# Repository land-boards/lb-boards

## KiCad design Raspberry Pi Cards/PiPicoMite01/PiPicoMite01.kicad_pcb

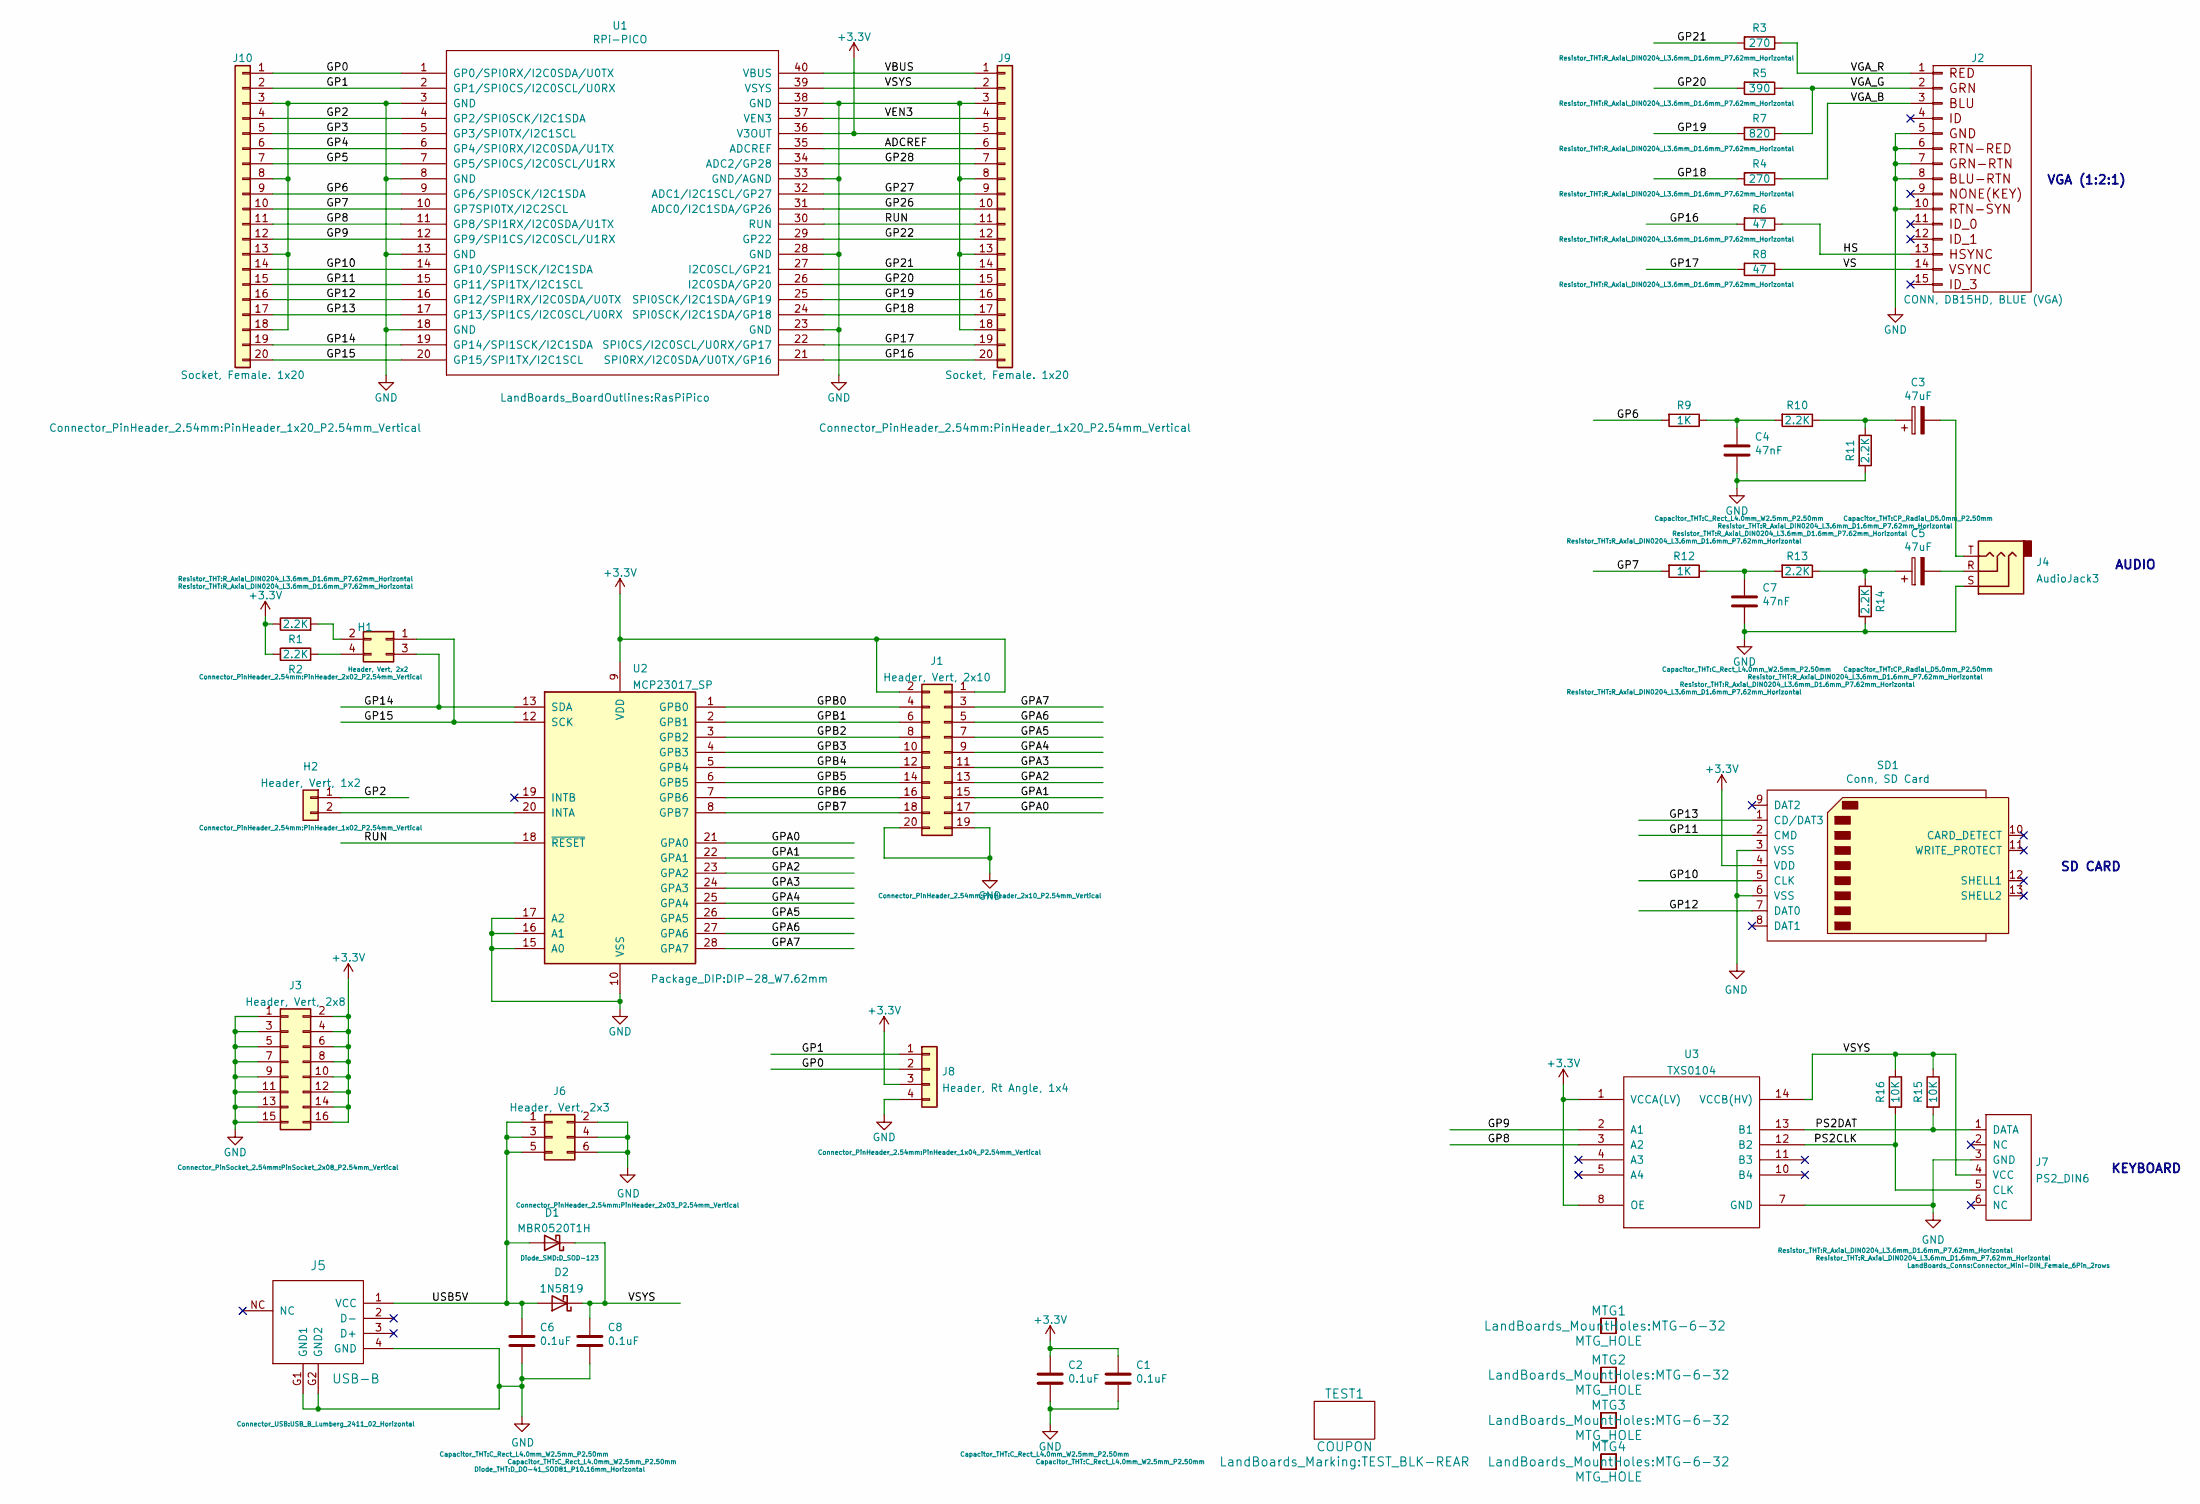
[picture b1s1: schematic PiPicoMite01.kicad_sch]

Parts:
C1, C2, C6, C8: 0.1uF; C_Rect_L4.0mm_W2.5mm_P2.50mm
C3, C5: 47uF; CP_Radial_D5.0mm_P2.50mm
C4, C7: 47nF; C_Rect_L4.0mm_W2.5mm_P2.50mm
D1: MBR0520T1H; D_SOD-123
D2: 1N5819; D_DO-41_SOD81_P10.16mm_Horizontal
H1: Header, Vert, 2x2; PinHeader_2x02_P2.54mm_Vertical
H2: Header, Vert, 1x2; PinHeader_1x02_P2.54mm_Vertical
J1: Header, Vert, 2x10; PinHeader_2x10_P2.54mm_Vertical
J2: CONN, DB15HD, BLUE (VGA); DB_15F-VGA-fixed
J3: Header, Vert, 2x8; PinSocket_2x08_P2.54mm_Vertical
J4: AudioJack3; Jack_3.5mm_CUI_SJ1-3523N_Horizontal
J5: USB-B; USB_B_Lumberg_2411_02_Horizontal
J6: Header, Vert, 2x3; PinHeader_2x03_P2.54mm_Vertical
J7: PS2_DIN6; Connector_Mini-DIN_Female_6Pin_2rows
J8: Header, Rt Angle, 1x4; PinHeader_1x04_P2.54mm_Vertical
J9, J10: Socket, Female. 1x20; PinHeader_1x20_P2.54mm_Vertical
MTG1, MTG2, MTG3, MTG4: MTG_HOLE; MTG-6-32
R1, R2, R10, R11, R13, R14: 2.2K; R_Axial_DIN0204_L3.6mm_D1.6mm_P7.62mm_Horizontal
R3, R4: 270; R_Axial_DIN0204_L3.6mm_D1.6mm_P7.62mm_Horizontal
R5: 390; R_Axial_DIN0204_L3.6mm_D1.6mm_P7.62mm_Horizontal
R6, R8: 47; R_Axial_DIN0204_L3.6mm_D1.6mm_P7.62mm_Horizontal
R7: 820; R_Axial_DIN0204_L3.6mm_D1.6mm_P7.62mm_Horizontal
R9, R12: 1K; R_Axial_DIN0204_L3.6mm_D1.6mm_P7.62mm_Horizontal
R15, R16: 10K; R_Axial_DIN0204_L3.6mm_D1.6mm_P7.62mm_Horizontal
SD1: Conn, SD Card; SD_CARD
TEST1: COUPON; TEST_BLK-REAR
U1: RPi-PICO; RasPiPico
U2: MCP23017_SP; DIP-28_W7.62mm
U3: TXS0104; SOIC-14_3.9x8.7mm_P1.27mm

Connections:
+3V3: C1.1, C2.1, J1.1, J1.2, J3.2, J3.4, J3.6, J3.8, J3.10, J3.12, J3.14, J3.16, J8.3, J9.5, R1.1, R2.1, SD1.4 (VDD), U1.36 (V3OUT), U2.9 (VDD), U3.1 (VCCA(LV)), U3.8 (OE)
/ADCREF: J9.6, U1.35 (ADCREF)
/GP0: J8.2, J10.1, U1.1 (GP0/SPI0RX/I2C0SDA/U0TX)
/GP1: J8.1, J10.2, U1.2 (GP1/SPI0CS/I2C0SCL/U0RX)
/GP2: H2.1, J10.4, U1.4 (GP2/SPI0SCK/I2C1SDA)
/GP3: J10.5, U1.5 (GP3/SPI0TX/I2C1SCL)
/GP4: J10.6, U1.6 (GP4/SPI0RX/I2C0SDA/U1TX)
/GP5: J10.7, U1.7 (GP5/SPI0CS/I2C0SCL/U1RX)
/GP6: J10.9, R9.2, U1.9 (GP6/SPI0SCK/I2C1SDA)
/GP7: J10.10, R12.2, U1.10 (GP7SPI0TX/I2C2SCL)
/GP8: J10.11, U1.11 (GP8/SPI1RX/I2C0SDA/U1TX), U3.3 (A2)
/GP9: J10.12, U1.12 (GP9/SPI1CS/I2C0SCL/U1RX), U3.2 (A1)
/GP10: J10.14, SD1.5 (CLK), U1.14 (GP10/SPI1SCK/I2C1SDA)
/GP11: J10.15, SD1.2 (CMD), U1.15 (GP11/SPI1TX/I2C1SCL)
/GP12: J10.16, SD1.7 (DAT0), U1.16 (GP12/SPI1RX/I2C0SDA/U0TX)
/GP13: J10.17, SD1.1 (CD/DAT3), U1.17 (GP13/SPI1CS/I2C0SCL/U0RX)
/GP14: H1.3, J10.19, U1.19 (GP14/SPI1SCK/I2C1SDA), U2.13 (SDA)
/GP15: H1.1, J10.20, U1.20 (GP15/SPI1TX/I2C1SCL), U2.12 (SCK)
/GP16: J9.20, R6.2, U1.21 (SPI0RX/I2C0SDA/U0TX/GP16)
/GP17: J9.19, R8.2, U1.22 (SPI0CS/I2C0SCL/U0RX/GP17)
/GP18: J9.17, R4.2, U1.24 (SPI0SCK/I2C1SDA/GP18)
/GP19: J9.16, R7.2, U1.25 (SPI0SCK/I2C1SDA/GP19)
/GP20: J9.15, R5.2, U1.26 (I2C0SDA/GP20)
/GP21: J9.14, R3.2, U1.27 (I2C0SCL/GP21)
/GP22: J9.12, U1.29 (GP22)
/GP26: J9.10, U1.31 (ADC0/I2C1SDA/GP26)
/GP27: J9.9, U1.32 (ADC1/I2C1SCL/GP27)
/GP28: J9.7, U1.34 (ADC2/GP28)
/GPA0: J1.17, U2.21 (GPA0)
/GPA1: J1.15, U2.22 (GPA1)
/GPA2: J1.13, U2.23 (GPA2)
/GPA3: J1.11, U2.24 (GPA3)
/GPA4: J1.9, U2.25 (GPA4)
/GPA5: J1.7, U2.26 (GPA5)
/GPA6: J1.5, U2.27 (GPA6)
/GPA7: J1.3, U2.28 (GPA7)
/GPB0: J1.4, U2.1 (GPB0)
/GPB1: J1.6, U2.2 (GPB1)
/GPB2: J1.8, U2.3 (GPB2)
/GPB3: J1.10, U2.4 (GPB3)
/GPB4: J1.12, U2.5 (GPB4)
/GPB5: J1.14, U2.6 (GPB5)
/GPB6: J1.16, U2.7 (GPB6)
/GPB7: J1.18, U2.8 (GPB7)
/HS: J2.13, R6.1
/PS2CLK: J7.5 (CLK), R16.2, U3.12 (B2)
/PS2DAT: J7.1 (DATA), R15.2, U3.13 (B1)
/RUN: J9.11, U1.30 (RUN), U2.18 (~RESET)
/USB5V: C6.1, D1.2 (A), D2.2 (A), J5.1 (VCC), J6.1, J6.3, J6.5
/VBUS: J9.1, U1.40 (VBUS)
/VEN3: J9.4, U1.37 (VEN3)
/VGA_B: J2.3, R4.1
/VGA_G: J2.2, R5.1, R7.1
/VGA_R: J2.1, R3.1
/VS: J2.14, R8.1
/VSYS: C8.1, D1.1 (K), D2.1 (K), J7.4 (VCC), J9.2, R15.1, R16.1, U1.39 (VSYS), U3.14 (VCCB(HV))
GND: C1.2, C2.2, C4.2, C6.2, C7.2, C8.2, J1.19, J1.20, J2.5, J2.6, J2.7, J2.8, J2.10, J3.1, J3.3, J3.5, J3.7, J3.9, J3.11, J3.13, J3.15, J4.S, J5.4 (GND), J5.G1 (GND1), J5.G2 (GND2), J6.2, J6.4, J6.6, J7.3 (GND), J8.4, J9.3, J9.8, J9.13, J9.18, J10.3, J10.8, J10.13, J10.18, R11.2, R14.1, SD1.3 (VSS), SD1.6 (VSS), U1.3 (GND), U1.8 (GND), U1.13 (GND), U1.18 (GND), U1.23 (GND), U1.28 (GND), U1.33 (GND/AGND), U1.38 (GND), U2.10 (VSS), U2.15 (A0), U2.16 (A1), U2.17 (A2), U3.7 (GND)
unnamed: C3.1, R10.1, R11.1
unnamed: C3.2, J4.T
unnamed: C4.1, R9.1, R10.2
unnamed: C5.1, R13.1, R14.2
unnamed: C5.2, J4.R
unnamed: C7.1, R12.1, R13.2
unnamed: H1.2, R1.2
unnamed: H1.4, R2.2
unnamed: H2.2, U2.20 (INTA)

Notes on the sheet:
KEYBOARD
AUDIO
VGA (1:2:1)
SD CARD

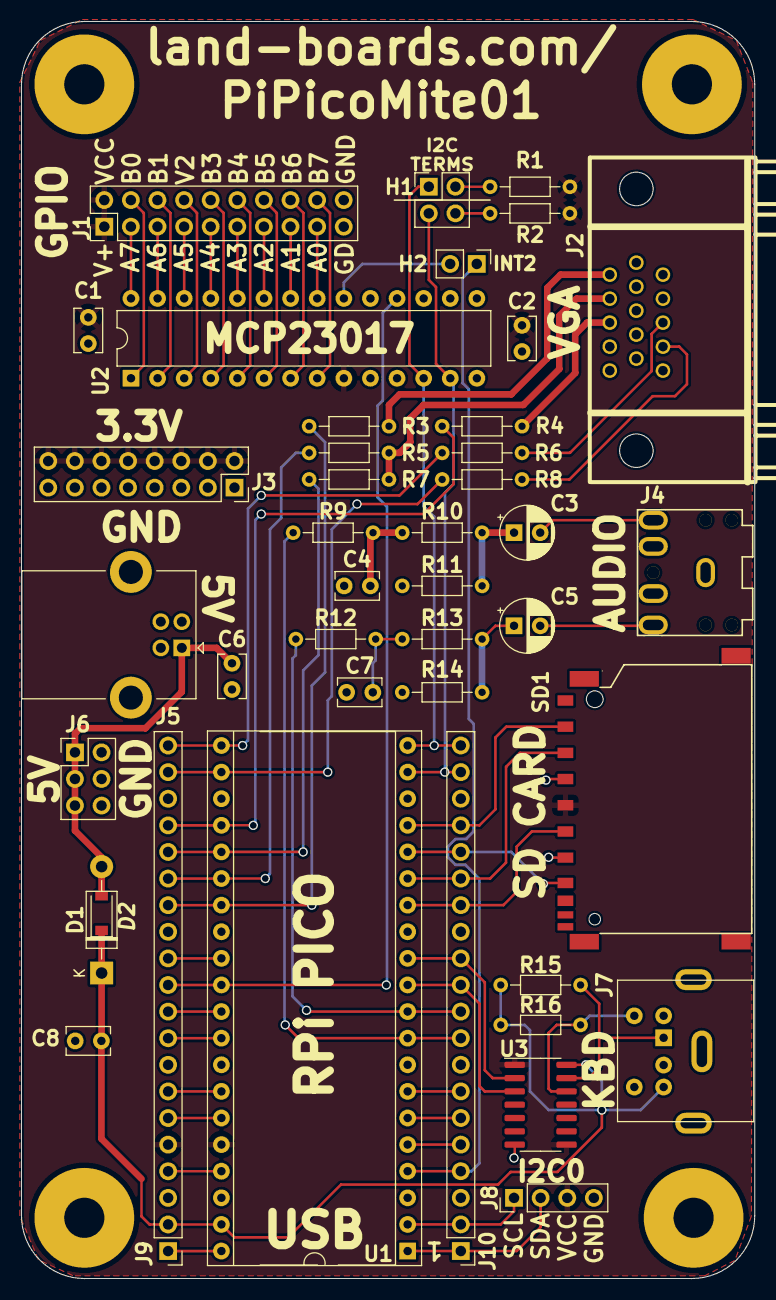
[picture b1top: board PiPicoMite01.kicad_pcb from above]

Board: 2 copper layers, 70.0 x 120.0 mm, 47 parts (0 on the bottom side), 66 nets.

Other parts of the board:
TEST: COUPON; TEST_BLK-REAR

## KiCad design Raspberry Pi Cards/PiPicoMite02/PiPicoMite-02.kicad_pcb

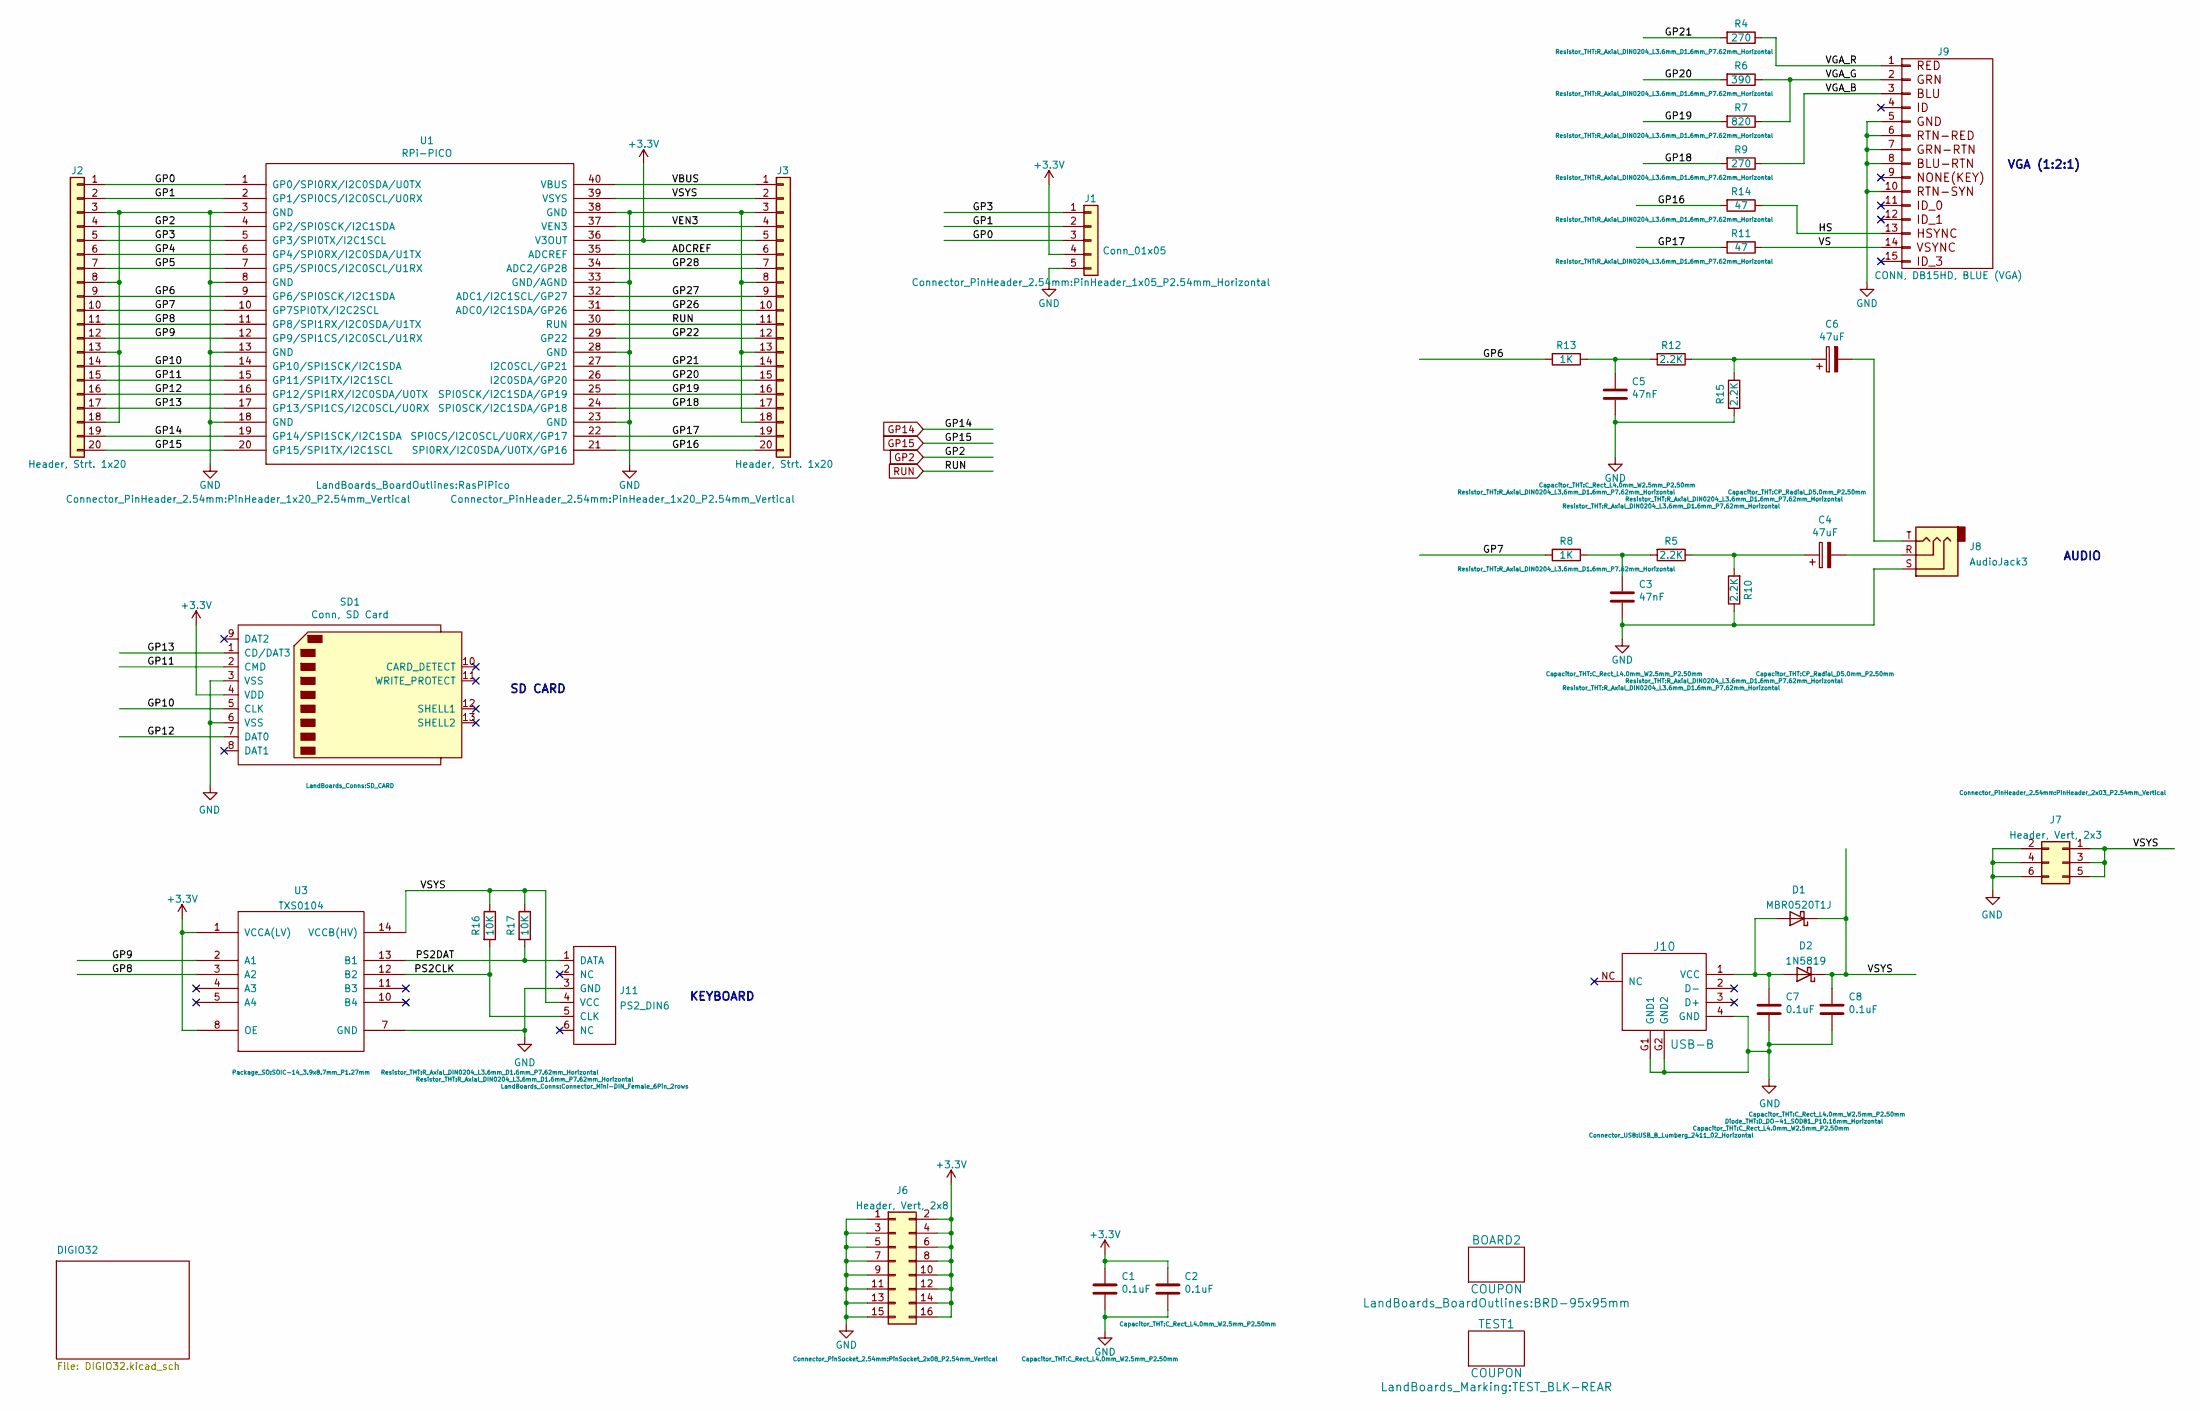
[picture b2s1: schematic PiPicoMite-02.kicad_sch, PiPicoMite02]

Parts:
BOARD2: COUPON; BRD-95x95mm
C1, C2, C7, C8: 0.1uF; C_Rect_L4.0mm_W2.5mm_P2.50mm
C3, C5: 47nF; C_Rect_L4.0mm_W2.5mm_P2.50mm
C4, C6: 47uF; CP_Radial_D5.0mm_P2.50mm
D1: MBR0520T1J; D_SOD-123
D2: 1N5819; D_DO-41_SOD81_P10.16mm_Horizontal
J1: Conn_01x05; PinHeader_1x05_P2.54mm_Horizontal
J2, J3: Header, Strt. 1x20; PinHeader_1x20_P2.54mm_Vertical
J6: Header, Vert, 2x8; PinSocket_2x08_P2.54mm_Vertical
J7: Header, Vert, 2x3; PinHeader_2x03_P2.54mm_Vertical
J8: AudioJack3; Jack_3.5mm_CUI_SJ1-3523N_Horizontal
J9: CONN, DB15HD, BLUE (VGA); DB_15F-VGA-fixed
J10: USB-B; USB_B_Lumberg_2411_02_Horizontal
J11: PS2_DIN6; Connector_Mini-DIN_Female_6Pin_2rows
R4, R9: 270; R_Axial_DIN0204_L3.6mm_D1.6mm_P7.62mm_Horizontal
R5, R10, R12, R15: 2.2K; R_Axial_DIN0204_L3.6mm_D1.6mm_P7.62mm_Horizontal
R6: 390; R_Axial_DIN0204_L3.6mm_D1.6mm_P7.62mm_Horizontal
R7: 820; R_Axial_DIN0204_L3.6mm_D1.6mm_P7.62mm_Horizontal
R8, R13: 1K; R_Axial_DIN0204_L3.6mm_D1.6mm_P7.62mm_Horizontal
R11, R14: 47; R_Axial_DIN0204_L3.6mm_D1.6mm_P7.62mm_Horizontal
R16, R17: 10K; R_Axial_DIN0204_L3.6mm_D1.6mm_P7.62mm_Horizontal
SD1: Conn, SD Card; SD_CARD
TEST1: COUPON; TEST_BLK-REAR
U1: RPi-PICO; RasPiPico
U3: TXS0104; SOIC-14_3.9x8.7mm_P1.27mm

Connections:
+3V3: C1.1, C2.1, J1.4, J3.5, J6.2, J6.4, J6.6, J6.8, J6.10, J6.12, J6.14, J6.16, SD1.4 (VDD), U1.36 (V3OUT), U3.1 (VCCA(LV)), U3.8 (OE); also elsewhere on the board
/ADCREF: J3.6, U1.35 (ADCREF)
/GP0: J1.3, J2.1, U1.1 (GP0/SPI0RX/I2C0SDA/U0TX)
/GP1: J1.2, J2.2, U1.2 (GP1/SPI0CS/I2C0SCL/U0RX)
/GP3: J1.1, J2.5, U1.5 (GP3/SPI0TX/I2C1SCL)
/GP4: J2.6, U1.6 (GP4/SPI0RX/I2C0SDA/U1TX)
/GP5: J2.7, U1.7 (GP5/SPI0CS/I2C0SCL/U1RX)
/GP6: J2.9, R13.2, U1.9 (GP6/SPI0SCK/I2C1SDA)
/GP7: J2.10, R8.2, U1.10 (GP7SPI0TX/I2C2SCL)
/GP8: J2.11, U1.11 (GP8/SPI1RX/I2C0SDA/U1TX), U3.3 (A2)
/GP9: J2.12, U1.12 (GP9/SPI1CS/I2C0SCL/U1RX), U3.2 (A1)
/GP10: J2.14, SD1.5 (CLK), U1.14 (GP10/SPI1SCK/I2C1SDA)
/GP11: J2.15, SD1.2 (CMD), U1.15 (GP11/SPI1TX/I2C1SCL)
/GP12: J2.16, SD1.7 (DAT0), U1.16 (GP12/SPI1RX/I2C0SDA/U0TX)
/GP13: J2.17, SD1.1 (CD/DAT3), U1.17 (GP13/SPI1CS/I2C0SCL/U0RX)
/GP16: J3.20, R14.2, U1.21 (SPI0RX/I2C0SDA/U0TX/GP16)
/GP17: J3.19, R11.2, U1.22 (SPI0CS/I2C0SCL/U0RX/GP17)
/GP18: J3.17, R9.2, U1.24 (SPI0SCK/I2C1SDA/GP18)
/GP19: J3.16, R7.2, U1.25 (SPI0SCK/I2C1SDA/GP19)
/GP20: J3.15, R6.2, U1.26 (I2C0SDA/GP20)
/GP21: J3.14, R4.2, U1.27 (I2C0SCL/GP21)
/GP22: J3.12, U1.29 (GP22)
/GP26: J3.10, U1.31 (ADC0/I2C1SDA/GP26)
/GP27: J3.9, U1.32 (ADC1/I2C1SCL/GP27)
/GP28: J3.7, U1.34 (ADC2/GP28)
/HS: J9.13, R14.1
/PS2CLK: J11.5 (CLK), R16.2, U3.12 (B2)
/PS2DAT: J11.1 (DATA), R17.2, U3.13 (B1)
/VBUS: J3.1, U1.40 (VBUS)
/VEN3: J3.4, U1.37 (VEN3)
/VGA_B: J9.3, R9.1
/VGA_G: J9.2, R6.1, R7.1
/VGA_R: J9.1, R4.1
/VS: J9.14, R11.1
/VSYS: C8.1, D1.1 (K), D2.1 (K), J3.2, J7.1, J7.3, J7.5, J11.4 (VCC), R16.1, R17.1, U1.39 (VSYS), U3.14 (VCCB(HV))
GND: C1.2, C2.2, C3.2, C5.2, C7.2, C8.2, J1.5, J2.3, J2.8, J2.13, J2.18, J3.3, J3.8, J3.13, J3.18, J6.1, J6.3, J6.5, J6.7, J6.9, J6.11, J6.13, J6.15, J7.2, J7.4, J7.6, J8.S, J9.5, J9.6, J9.7, J9.8, J9.10, J10.4 (GND), J10.G1 (GND1), J10.G2 (GND2), J11.3 (GND), R10.1, R15.2, SD1.3 (VSS), SD1.6 (VSS), U1.3 (GND), U1.8 (GND), U1.13 (GND), U1.18 (GND), U1.23 (GND), U1.28 (GND), U1.33 (GND/AGND), U1.38 (GND), U3.7 (GND); also elsewhere on the board
GP2: J2.4, U1.4 (GP2/SPI0SCK/I2C1SDA); also elsewhere on the board
GP14: J2.19, U1.19 (GP14/SPI1SCK/I2C1SDA); also elsewhere on the board
GP15: J2.20, U1.20 (GP15/SPI1TX/I2C1SCL); also elsewhere on the board
unnamed: C3.1, R5.2, R8.1
unnamed: C4.1, R5.1, R10.2
unnamed: C4.2, J8.R
unnamed: C5.1, R12.2, R13.1
unnamed: C6.1, R12.1, R15.1
unnamed: C6.2, J8.T
unnamed: C7.1, D1.2 (A), D2.2 (A), J10.1 (VCC)
RUN: J3.11, U1.30 (RUN); also elsewhere on the board

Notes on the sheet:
KEYBOARD
AUDIO
VGA (1:2:1)
SD CARD

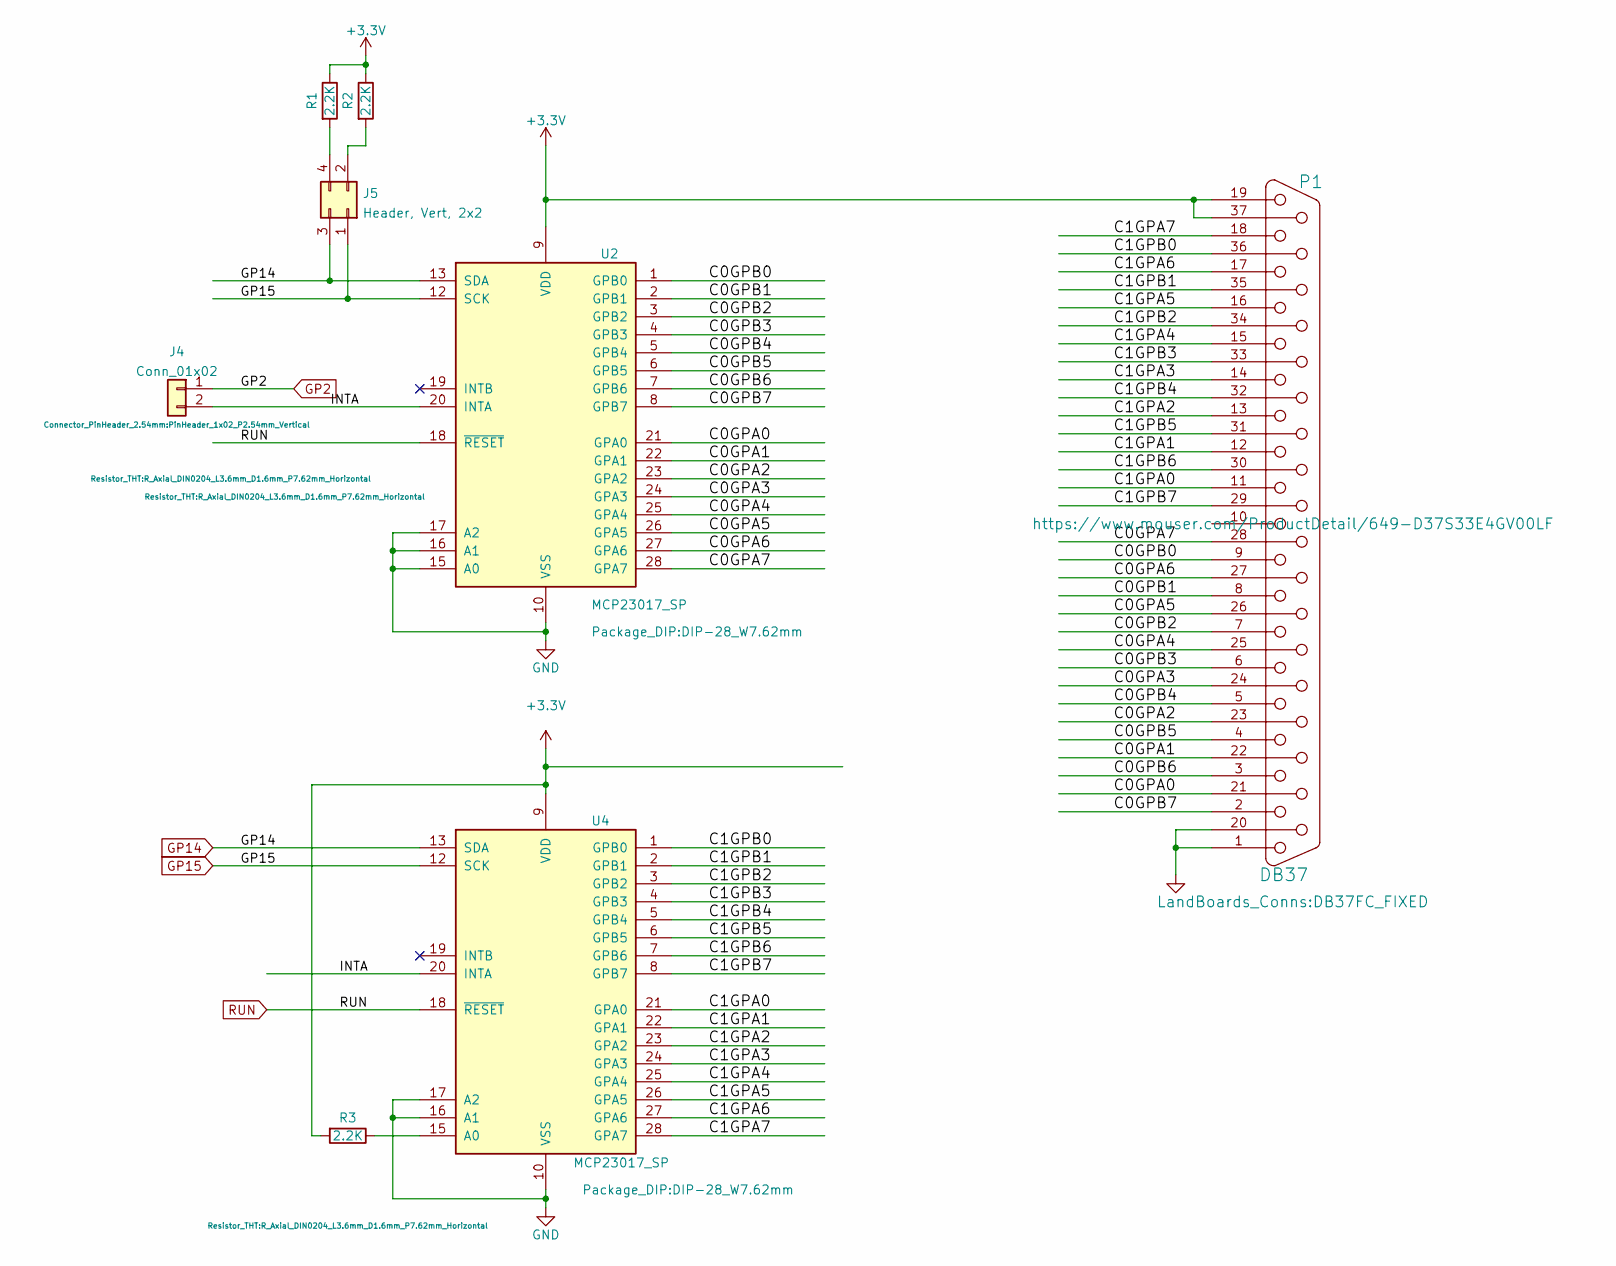
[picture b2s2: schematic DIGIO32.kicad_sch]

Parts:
J4: Conn_01x02; PinHeader_1x02_P2.54mm_Vertical
J5: Header, Vert, 2x2; PinHeader_2x02_P2.54mm_Vertical
P1: DB37; DB37FC_FIXED
R1, R2, R3: 2.2K; R_Axial_DIN0204_L3.6mm_D1.6mm_P7.62mm_Horizontal
U2, U4: MCP23017_SP; DIP-28_W7.62mm

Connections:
+3V3: P1.19, P1.37, R1.1, R2.1, R3.2, U2.9 (VDD), U4.9 (VDD); also elsewhere on the board
/DIGIO32/C0GPA0: P1.21, U2.21 (GPA0)
/DIGIO32/C0GPA1: P1.22, U2.22 (GPA1)
/DIGIO32/C0GPA2: P1.23, U2.23 (GPA2)
/DIGIO32/C0GPA3: P1.24, U2.24 (GPA3)
/DIGIO32/C0GPA4: P1.25, U2.25 (GPA4)
/DIGIO32/C0GPA5: P1.26, U2.26 (GPA5)
/DIGIO32/C0GPA6: P1.27, U2.27 (GPA6)
/DIGIO32/C0GPA7: P1.28, U2.28 (GPA7)
/DIGIO32/C0GPB0: P1.9, U2.1 (GPB0)
/DIGIO32/C0GPB1: P1.8, U2.2 (GPB1)
/DIGIO32/C0GPB2: P1.7, U2.3 (GPB2)
/DIGIO32/C0GPB3: P1.6, U2.4 (GPB3)
/DIGIO32/C0GPB4: P1.5, U2.5 (GPB4)
/DIGIO32/C0GPB5: P1.4, U2.6 (GPB5)
/DIGIO32/C0GPB6: P1.3, U2.7 (GPB6)
/DIGIO32/C0GPB7: P1.2, U2.8 (GPB7)
/DIGIO32/C1GPA0: P1.11, U4.21 (GPA0)
/DIGIO32/C1GPA1: P1.12, U4.22 (GPA1)
/DIGIO32/C1GPA2: P1.13, U4.23 (GPA2)
/DIGIO32/C1GPA3: P1.14, U4.24 (GPA3)
/DIGIO32/C1GPA4: P1.15, U4.25 (GPA4)
/DIGIO32/C1GPA5: P1.16, U4.26 (GPA5)
/DIGIO32/C1GPA6: P1.17, U4.27 (GPA6)
/DIGIO32/C1GPA7: P1.18, U4.28 (GPA7)
/DIGIO32/C1GPB0: P1.36, U4.1 (GPB0)
/DIGIO32/C1GPB1: P1.35, U4.2 (GPB1)
/DIGIO32/C1GPB2: P1.34, U4.3 (GPB2)
/DIGIO32/C1GPB3: P1.33, U4.4 (GPB3)
/DIGIO32/C1GPB4: P1.32, U4.5 (GPB4)
/DIGIO32/C1GPB5: P1.31, U4.6 (GPB5)
/DIGIO32/C1GPB6: P1.30, U4.7 (GPB6)
/DIGIO32/C1GPB7: P1.29, U4.8 (GPB7)
/DIGIO32/INTA: J4.2, U2.20 (INTA), U4.20 (INTA)
GND: P1.1, P1.20, U2.10 (VSS), U2.15 (A0), U2.16 (A1), U2.17 (A2), U4.10 (VSS), U4.16 (A1), U4.17 (A2); also elsewhere on the board
GP2: J4.1; also elsewhere on the board
GP14: J5.3, U2.13 (SDA), U4.13 (SDA); also elsewhere on the board
GP15: J5.1, U2.12 (SCK), U4.12 (SCK); also elsewhere on the board
unnamed: J5.2, R2.2
unnamed: J5.4, R1.2
unnamed: R3.1, U4.15 (A0)
RUN: U2.18 (~RESET), U4.18 (~RESET); also elsewhere on the board

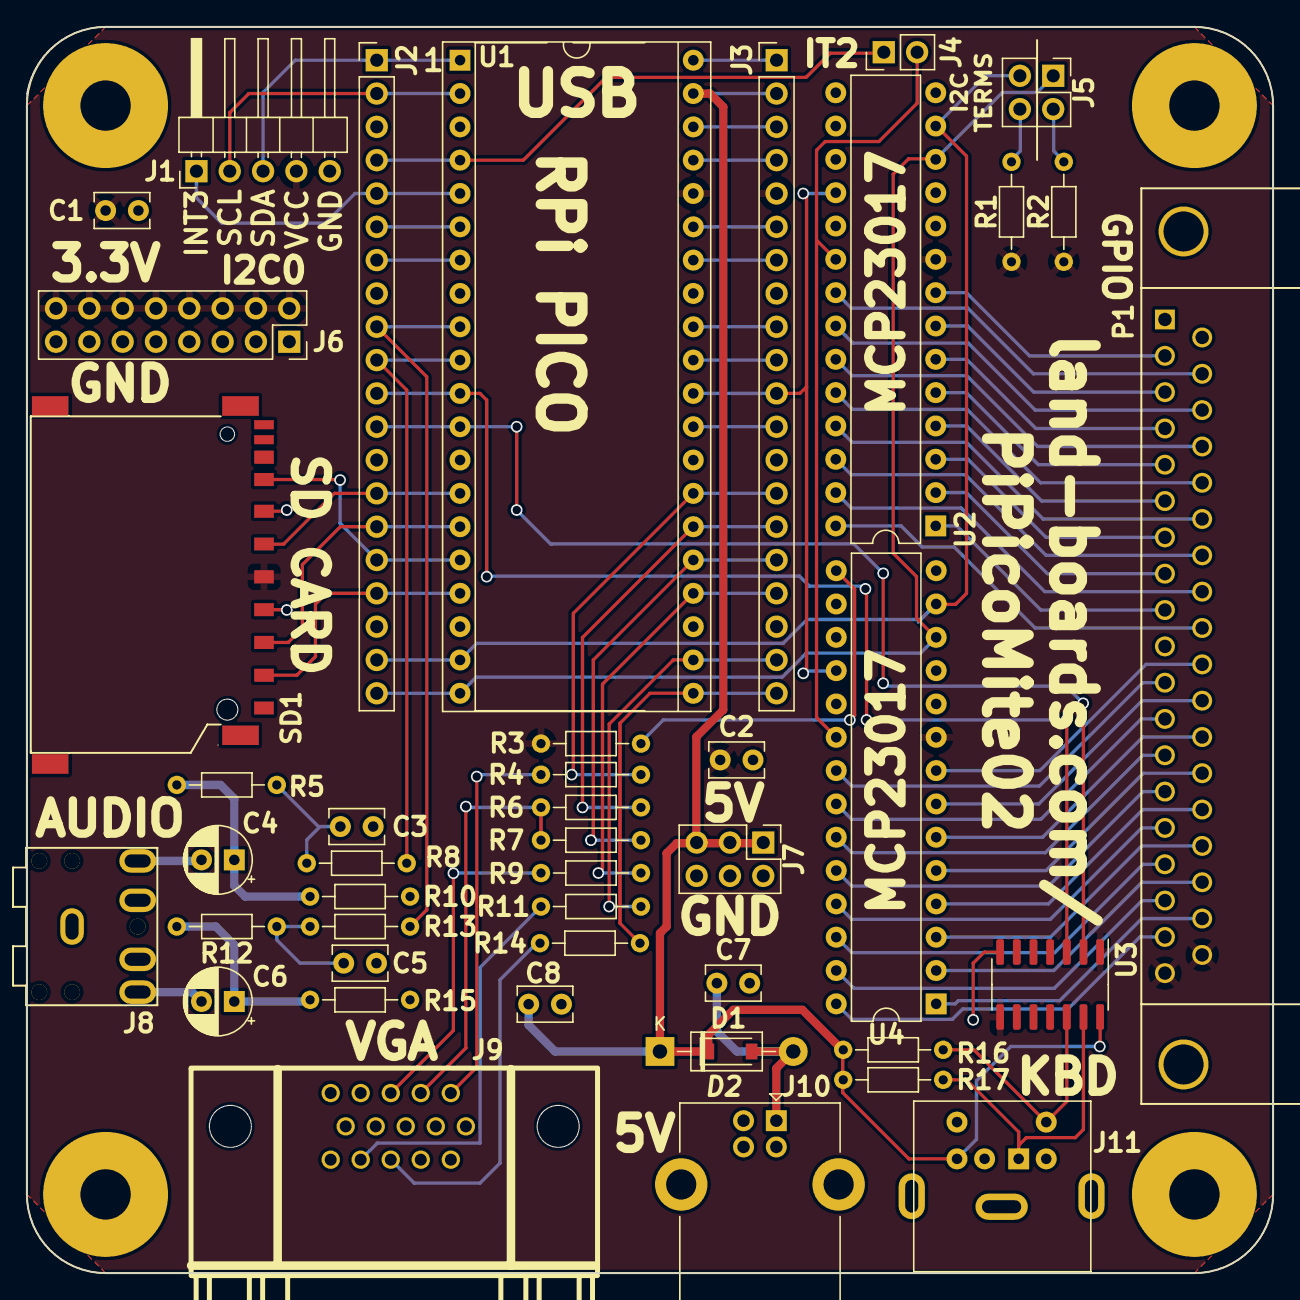
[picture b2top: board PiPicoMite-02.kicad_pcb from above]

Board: 2 copper layers, 95.0 x 95.0 mm, 46 parts (0 on the bottom side), 83 nets.

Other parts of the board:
TEST: COUPON; TEST_BLK-REAR

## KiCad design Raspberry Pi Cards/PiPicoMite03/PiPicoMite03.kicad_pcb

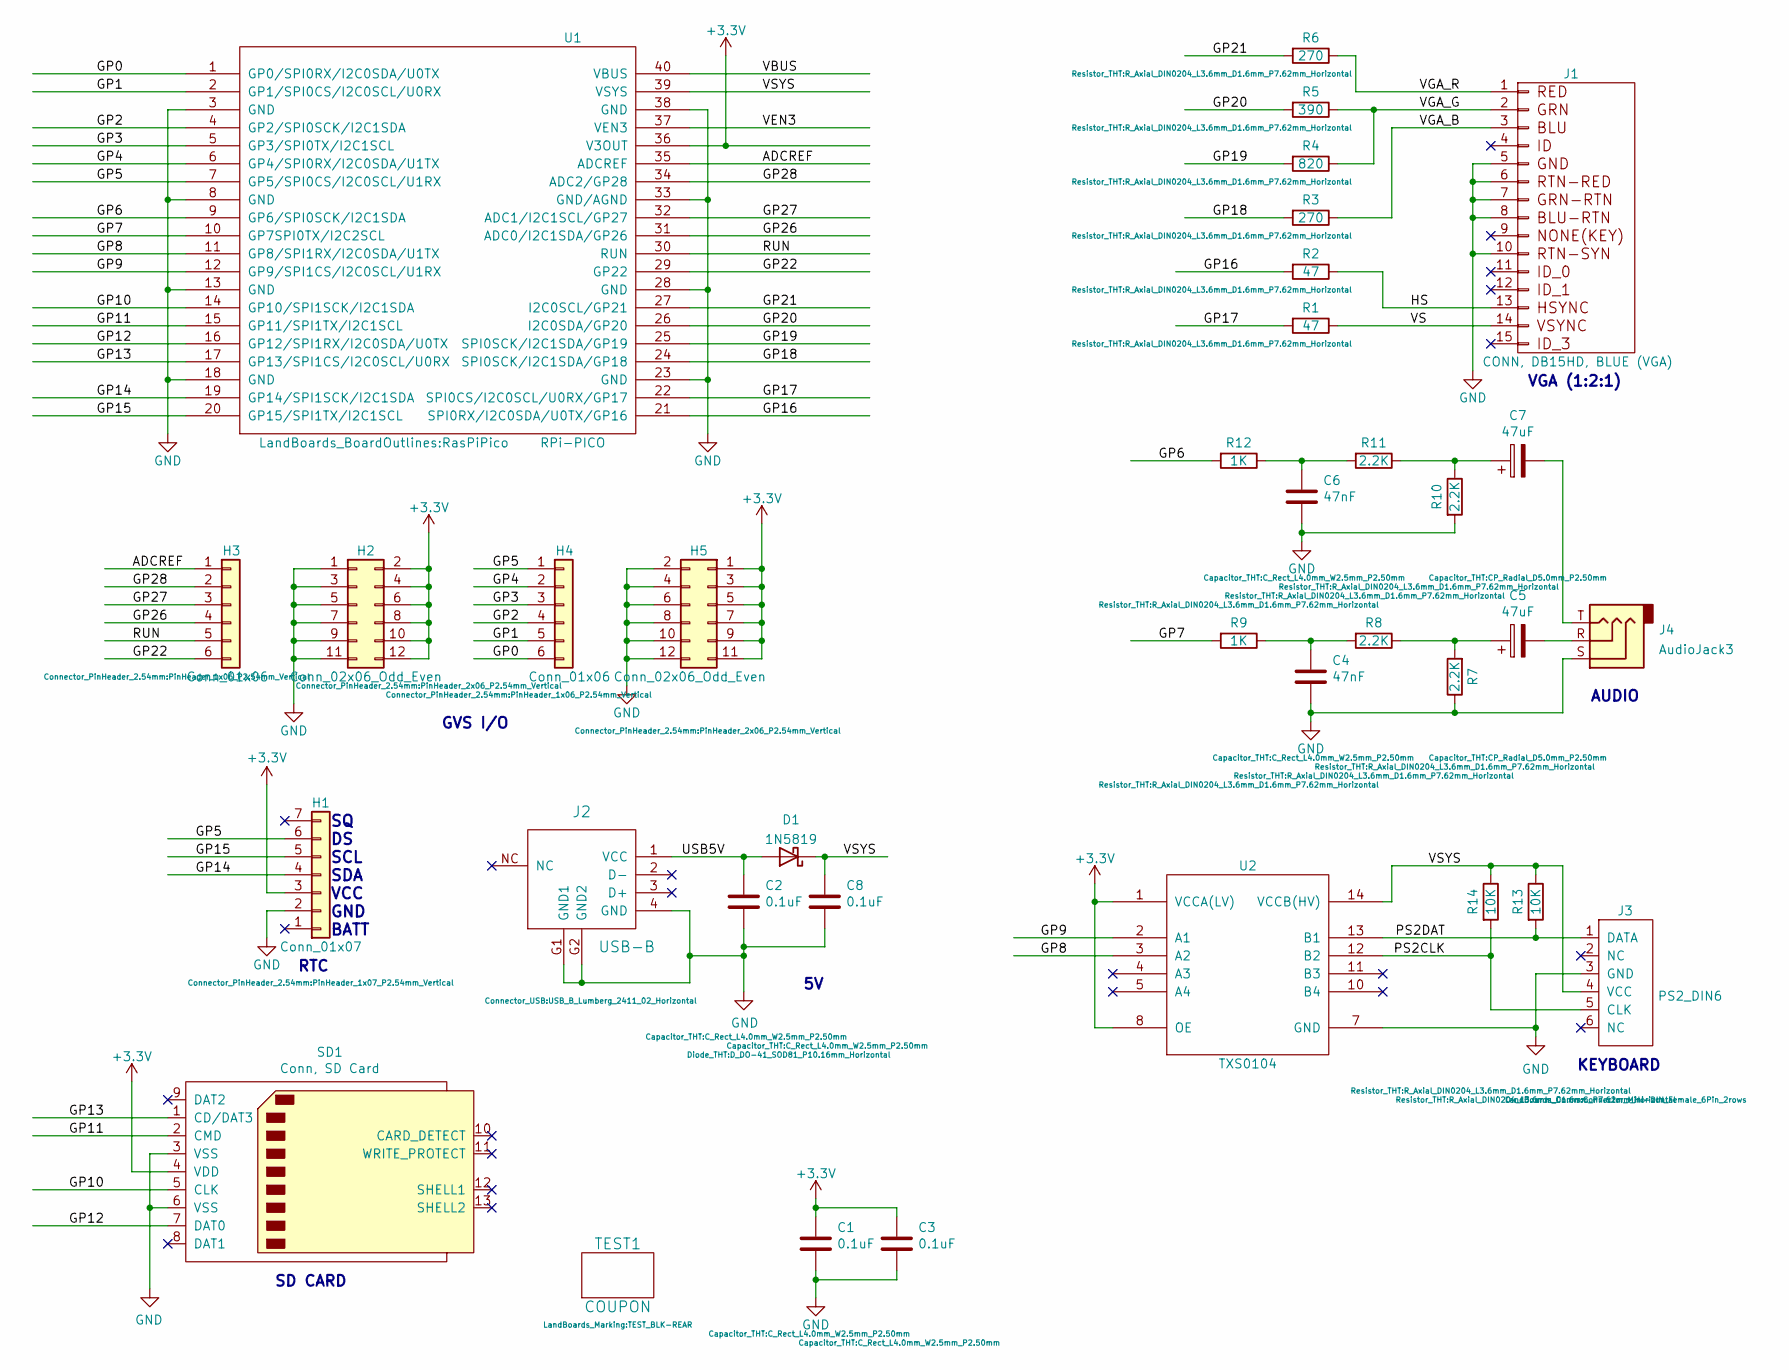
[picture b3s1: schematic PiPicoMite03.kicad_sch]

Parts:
C1, C2, C3, C8: 0.1uF; C_Rect_L4.0mm_W2.5mm_P2.50mm
C4, C6: 47nF; C_Rect_L4.0mm_W2.5mm_P2.50mm
C5, C7: 47uF; CP_Radial_D5.0mm_P2.50mm
D1: 1N5819; D_DO-41_SOD81_P10.16mm_Horizontal
H1: Conn_01x07; PinHeader_1x07_P2.54mm_Vertical
H2, H5: Conn_02x06_Odd_Even; PinHeader_2x06_P2.54mm_Vertical
H3, H4: Conn_01x06; PinHeader_1x06_P2.54mm_Vertical
J1: CONN, DB15HD, BLUE (VGA); DB_15F-VGA-fixed
J2: USB-B; USB_B_Lumberg_2411_02_Horizontal
J3: PS2_DIN6; Connector_Mini-DIN_Female_6Pin_2rows
J4: AudioJack3; Jack_3.5mm_CUI_SJ1-3523N_Horizontal
R1, R2: 47; R_Axial_DIN0204_L3.6mm_D1.6mm_P7.62mm_Horizontal
R3, R6: 270; R_Axial_DIN0204_L3.6mm_D1.6mm_P7.62mm_Horizontal
R4: 820; R_Axial_DIN0204_L3.6mm_D1.6mm_P7.62mm_Horizontal
R5: 390; R_Axial_DIN0204_L3.6mm_D1.6mm_P7.62mm_Horizontal
R7, R8, R10, R11: 2.2K; R_Axial_DIN0204_L3.6mm_D1.6mm_P7.62mm_Horizontal
R9, R12: 1K; R_Axial_DIN0204_L3.6mm_D1.6mm_P7.62mm_Horizontal
R13, R14: 10K; R_Axial_DIN0204_L3.6mm_D1.6mm_P7.62mm_Horizontal
SD1: Conn, SD Card; SD_CARD
TEST1: COUPON; TEST_BLK-REAR
U1: RPi-PICO; RasPiPico
U2: TXS0104; SOIC-14_3.9x8.7mm_P1.27mm

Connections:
+3V3: C1.1, C3.1, H1.3, H2.2, H2.4, H2.6, H2.8, H2.10, H2.12, H5.1, H5.3, H5.5, H5.7, H5.9, H5.11, SD1.4 (VDD), U1.36 (V3OUT), U2.1 (VCCA(LV)), U2.8 (OE)
/ADCREF: H3.1, U1.35 (ADCREF)
/GP0: H4.6, U1.1 (GP0/SPI0RX/I2C0SDA/U0TX)
/GP1: H4.5, U1.2 (GP1/SPI0CS/I2C0SCL/U0RX)
/GP2: H4.4, U1.4 (GP2/SPI0SCK/I2C1SDA)
/GP3: H4.3, U1.5 (GP3/SPI0TX/I2C1SCL)
/GP4: H4.2, U1.6 (GP4/SPI0RX/I2C0SDA/U1TX)
/GP5: H1.6, H4.1, U1.7 (GP5/SPI0CS/I2C0SCL/U1RX)
/GP6: R12.2, U1.9 (GP6/SPI0SCK/I2C1SDA)
/GP7: R9.2, U1.10 (GP7SPI0TX/I2C2SCL)
/GP8: U1.11 (GP8/SPI1RX/I2C0SDA/U1TX), U2.3 (A2)
/GP9: U1.12 (GP9/SPI1CS/I2C0SCL/U1RX), U2.2 (A1)
/GP10: SD1.5 (CLK), U1.14 (GP10/SPI1SCK/I2C1SDA)
/GP11: SD1.2 (CMD), U1.15 (GP11/SPI1TX/I2C1SCL)
/GP12: SD1.7 (DAT0), U1.16 (GP12/SPI1RX/I2C0SDA/U0TX)
/GP13: SD1.1 (CD/DAT3), U1.17 (GP13/SPI1CS/I2C0SCL/U0RX)
/GP14: H1.4, U1.19 (GP14/SPI1SCK/I2C1SDA)
/GP15: H1.5, U1.20 (GP15/SPI1TX/I2C1SCL)
/GP16: R2.2, U1.21 (SPI0RX/I2C0SDA/U0TX/GP16)
/GP17: R1.2, U1.22 (SPI0CS/I2C0SCL/U0RX/GP17)
/GP18: R3.2, U1.24 (SPI0SCK/I2C1SDA/GP18)
/GP19: R4.2, U1.25 (SPI0SCK/I2C1SDA/GP19)
/GP20: R5.2, U1.26 (I2C0SDA/GP20)
/GP21: R6.2, U1.27 (I2C0SCL/GP21)
/GP22: H3.6, U1.29 (GP22)
/GP26: H3.4, U1.31 (ADC0/I2C1SDA/GP26)
/GP27: H3.3, U1.32 (ADC1/I2C1SCL/GP27)
/GP28: H3.2, U1.34 (ADC2/GP28)
/HS: J1.13, R2.1
/PS2CLK: J3.5 (CLK), R14.2, U2.12 (B2)
/PS2DAT: J3.1 (DATA), R13.2, U2.13 (B1)
/RUN: H3.5, U1.30 (RUN)
/USB5V: C2.1, D1.2 (A), J2.1 (VCC)
/VBUS: U1.40 (VBUS)
/VEN3: U1.37 (VEN3)
/VGA_B: J1.3, R3.1
/VGA_G: J1.2, R4.1, R5.1
/VGA_R: J1.1, R6.1
/VS: J1.14, R1.1
/VSYS: C8.1, D1.1 (K), J3.4 (VCC), R13.1, R14.1, U1.39 (VSYS), U2.14 (VCCB(HV))
GND: C1.2, C2.2, C3.2, C4.2, C6.2, C8.2, H1.2, H2.1, H2.3, H2.5, H2.7, H2.9, H2.11, H5.2, H5.4, H5.6, H5.8, H5.10, H5.12, J1.5, J1.6, J1.7, J1.8, J1.10, J2.4 (GND), J2.G1 (GND1), J2.G2 (GND2), J3.3 (GND), J4.S, R7.1, R10.2, SD1.3 (VSS), SD1.6 (VSS), U1.3 (GND), U1.8 (GND), U1.13 (GND), U1.18 (GND), U1.23 (GND), U1.28 (GND), U1.33 (GND/AGND), U1.38 (GND), U2.7 (GND)
unnamed: C4.1, R8.2, R9.1
unnamed: C5.1, R7.2, R8.1
unnamed: C5.2, J4.R
unnamed: C6.1, R11.2, R12.1
unnamed: C7.1, R10.1, R11.1
unnamed: C7.2, J4.T

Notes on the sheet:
GVS I/O
RTC
SQ DS SCL SDA VCC GND BATT
KEYBOARD
AUDIO
VGA (1:2:1)
SD CARD
